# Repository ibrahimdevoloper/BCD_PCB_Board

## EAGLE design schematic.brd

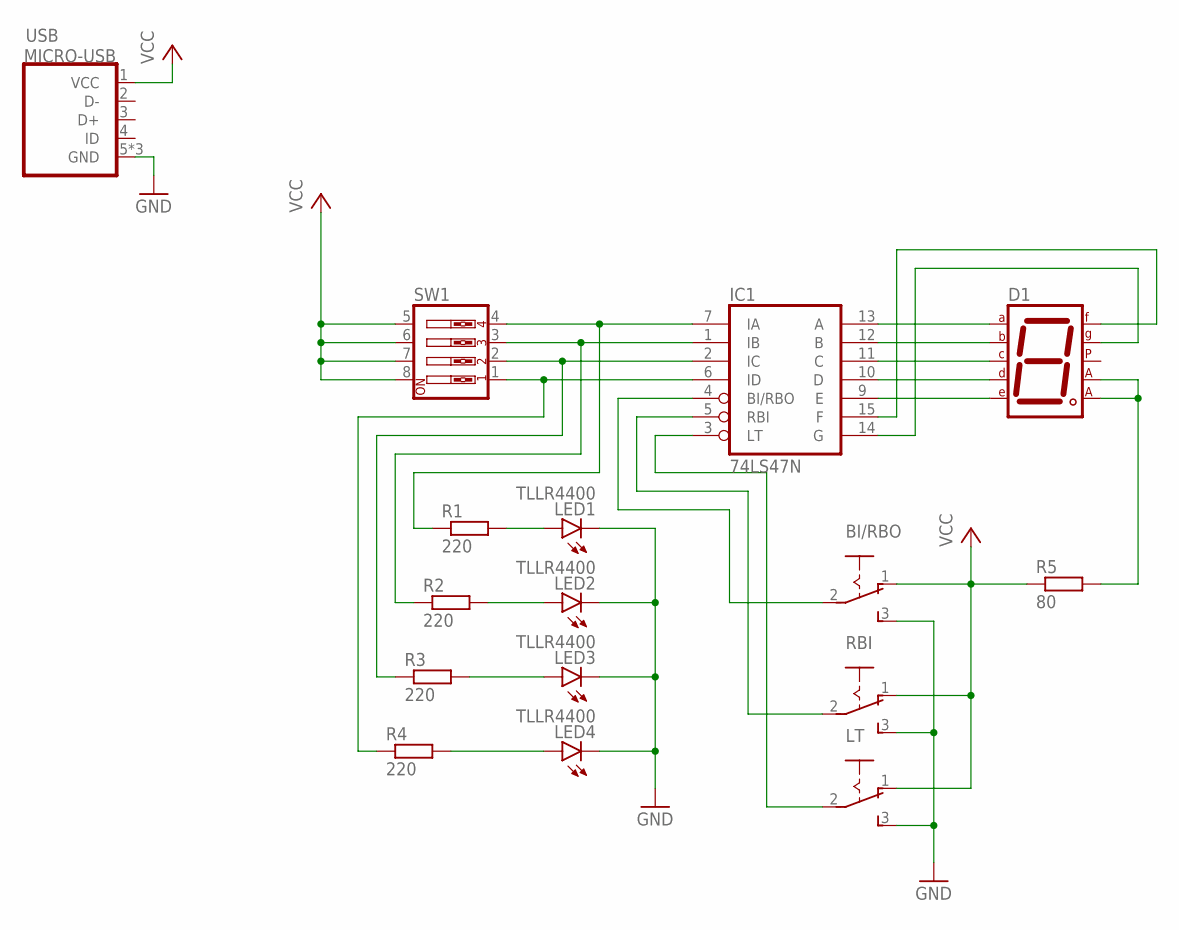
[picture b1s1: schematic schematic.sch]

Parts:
BI/RBO: 255SB
D1: 7SEG-CA; 7SEG-13
IC1: 74LS47N; DIL16
LED1, LED2, LED3, LED4: TLLR4400; LED3MM
LT: 255SB
R1, R2, R3, R4: 220; 0207/10
R5: 80; 0207/10
RBI: 255SB
SW1: SW_DIP-4; EDG-04
USB: MICRO-USB

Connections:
GND: BI/RBO.3 (S), IC1.8 (GND), LED1.K (C), LED2.K (C), LED3.K (C), LED4.K (C), LT.3 (S), RBI.3 (S), USB.5 (GND), USB.GND1 (GND), USB.GND2 (GND)
unnamed: IC1.7 (IA), R1.1, SW1.4
unnamed: IC1.1 (IB), R2.1, SW1.3
unnamed: IC1.2 (IC), R3.1, SW1.2
unnamed: IC1.6 (ID), R4.1, SW1.1
unnamed: LED1.A, R1.2
unnamed: D1.7 (A), IC1.13 (A)
unnamed: LED2.A, R2.2
unnamed: D1.6 (B), IC1.12 (B)
unnamed: D1.4 (C), IC1.11 (C)
unnamed: LED3.A, R3.2
unnamed: LED4.A, R4.2
unnamed: D1.2 (D), IC1.10 (D)
unnamed: BI/RBO.2, IC1.4 (BI/RBO)
unnamed: IC1.5 (RBI), RBI.2
unnamed: IC1.3 (LT), LT.2
unnamed: D1.1 (E), IC1.9 (E)
unnamed: D1.9 (F), IC1.15 (F)
unnamed: D1.10 (G), IC1.14 (G)
unnamed: D1.3 (CA1), D1.8 (CA2), R5.2
VCC: BI/RBO.1 (O), IC1.16 (VCC), LT.1 (O), R5.1, RBI.1 (O), SW1.5, SW1.6, SW1.7, SW1.8, USB.1 (VCC)

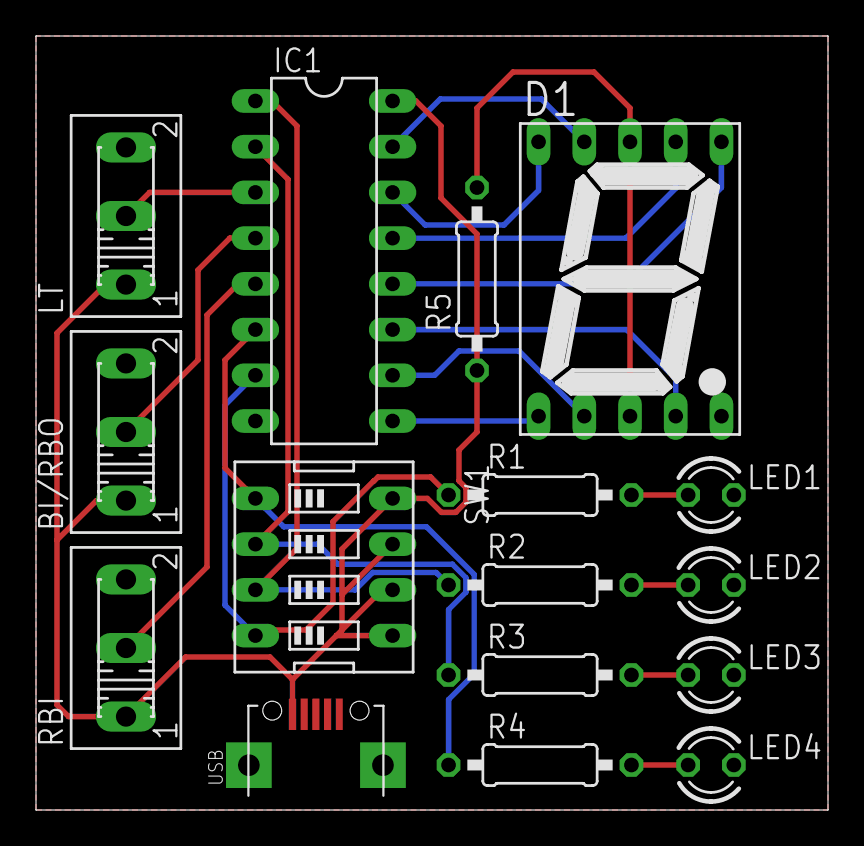
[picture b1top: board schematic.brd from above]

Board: 2 copper layers, 44.0 x 43.0 mm, 16 parts (0 on the bottom side), 21 nets.
